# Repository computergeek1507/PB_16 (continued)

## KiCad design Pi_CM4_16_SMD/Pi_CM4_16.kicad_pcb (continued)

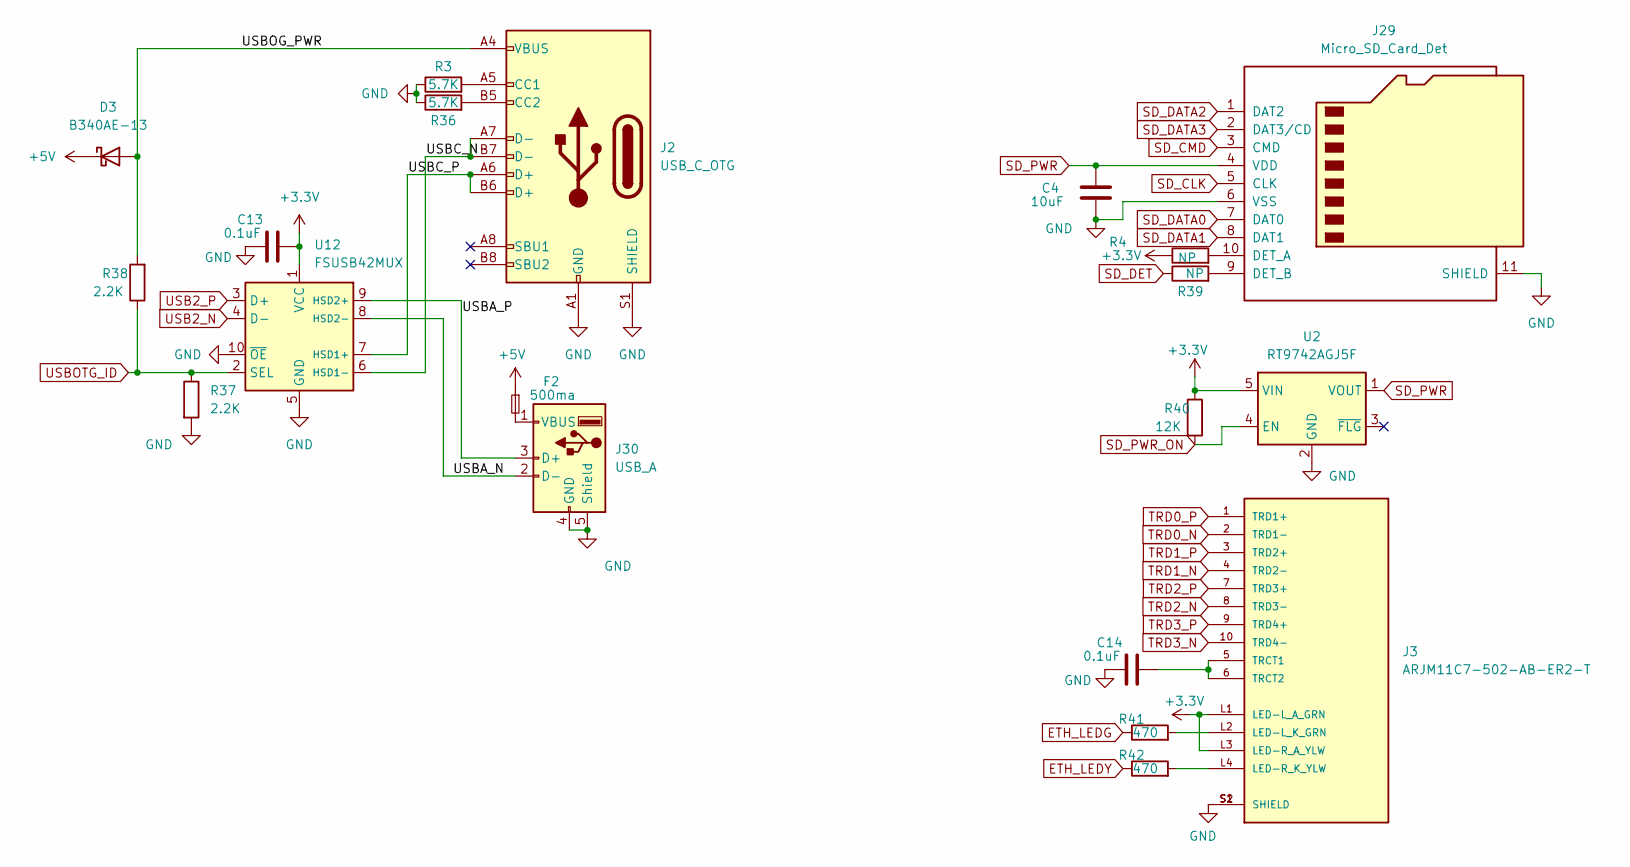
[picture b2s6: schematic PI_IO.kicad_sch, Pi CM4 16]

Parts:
C4: 10uF; C_0603_1608Metric_Pad1.08x0.95mm_HandSolder
C13, C14: 0.1uF; C_0603_1608Metric_Pad1.08x0.95mm_HandSolder; MPN CL10B104KB8NNWC; Digi-Key_PN 1276-1935-2-ND
D3: B340AE-13; D_SMA
F2: 500ma; Fuse_BelFuse_0ZRE0005FF_L8.3mm_W3.8mm
J2: USB_C_OTG; TYPE-C-31-M-12
J3: ARJM11C7-502-AB-ER2-T; ABRACON_ARJM11C7-502-AB-ER2-T; PARTREV 04.22.2019
J29: Micro_SD_Card_Det; microSD_HC_Molex_104031-0811
J30: USB_A; USB_A_Molex_105057_Vertical
R3, R36: 5.7K; R_0603_1608Metric_Pad0.98x0.95mm_HandSolder
R4, R39: NP; R_0603_1608Metric_Pad0.98x0.95mm_HandSolder
R37, R38: 2.2K; R_0603_1608Metric_Pad0.98x0.95mm_HandSolder
R40: 12K; R_0603_1608Metric_Pad0.98x0.95mm_HandSolder
R41, R42: 470; R_0603_1608Metric_Pad0.98x0.95mm_HandSolder
U2: RT9742AGJ5F; TSOT-23-5
U12: FSUSB42MUX; MSOP-10_3x3mm_P0.5mm

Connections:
+3.3V: C13.1, J3.L1 (LED-L_A_GRN), J3.L3 (LED-R_A_YLW), R4.1, R40.1, U2.5 (VIN), U12.1 (VCC); also elsewhere on the board
+5V: D3.1 (K), F2.1; also elsewhere on the board
/PI IO/USBA_N: J30.2 (D-), U12.8 (HSD2-)
/PI IO/USBA_P: J30.3 (D+), U12.9 (HSD2+)
/PI IO/USBC_N: J2.A7 (D-), J2.B7 (D-), U12.6 (HSD1-)
/PI IO/USBC_P: J2.A6 (D+), J2.B6 (D+), U12.7 (HSD1+)
/PI IO/USBOG_PWR: D3.2 (A), J2.A4 (VBUS), J2.A9 (VBUS), J2.B4 (VBUS), J2.B9 (VBUS), R38.2
ETH_LEDG: R41.1; also elsewhere on the board
ETH_LEDY: R42.1; also elsewhere on the board
GND: C4.1, C13.2, C14.2, J2.A1 (GND), J2.A12 (GND), J2.B1 (GND), J2.B12 (GND), J2.S1 (SHIELD), J3.S1 (SHIELD), J3.S2 (SHIELD), J29.6 (VSS), J29.11 (SHIELD), J30.4 (GND), J30.5 (Shield), R3.1, R36.1, R37.2, U2.2 (GND), U12.5 (GND), U12.10 (~OE); also elsewhere on the board
unnamed: C14.1, J3.5 (TRCT1), J3.6 (TRCT2)
unnamed: F2.2, J30.1 (VBUS)
unnamed: J2.A5 (CC1), R3.2
unnamed: J2.B5 (CC2), R36.2
unnamed: J3.L2 (LED-L_K_GRN), R41.2
unnamed: J3.L4 (LED-R_K_YLW), R42.2
unnamed: J29.9 (DET_B), R39.2
unnamed: J29.10 (DET_A), R4.2
SD_CLK: J29.5 (CLK); also elsewhere on the board
SD_CMD: J29.3 (CMD); also elsewhere on the board
SD_DATA0: J29.7 (DAT0); also elsewhere on the board
SD_DATA1: J29.8 (DAT1); also elsewhere on the board
SD_DATA2: J29.1 (DAT2); also elsewhere on the board
SD_DATA3: J29.2 (DAT3/CD); also elsewhere on the board
SD_DET: R39.1; also elsewhere on the board
SD_PWR: C4.2, J29.4 (VDD), U2.1 (VOUT)
SD_PWR_ON: R40.2, U2.4 (EN); also elsewhere on the board
TRD0_N: J3.2 (TRD1-); also elsewhere on the board
TRD0_P: J3.1 (TRD1+); also elsewhere on the board
TRD1_N: J3.4 (TRD2-); also elsewhere on the board
TRD1_P: J3.3 (TRD2+); also elsewhere on the board
TRD2_N: J3.8 (TRD3-); also elsewhere on the board
TRD2_P: J3.7 (TRD3+); also elsewhere on the board
TRD3_N: J3.10 (TRD4-); also elsewhere on the board
TRD3_P: J3.9 (TRD4+); also elsewhere on the board
USB2_N: U12.4 (D-); also elsewhere on the board
USB2_P: U12.3 (D+); also elsewhere on the board
USBOTG_ID: R37.1, R38.1, U12.2 (SEL); also elsewhere on the board

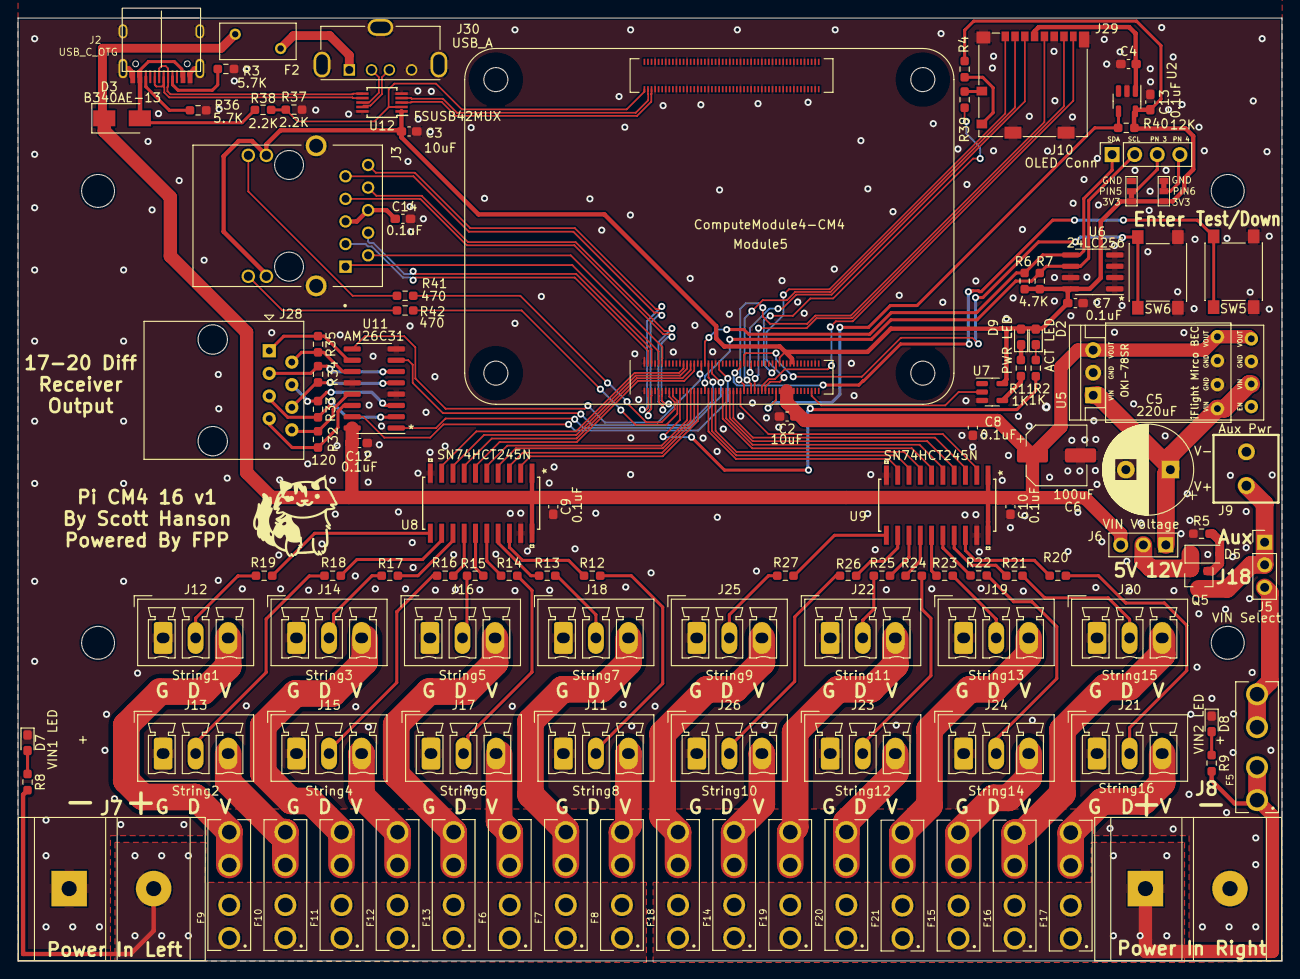
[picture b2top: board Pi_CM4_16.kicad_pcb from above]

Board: 2 copper layers, 142.1 x 106.0 mm, 117 parts (0 on the bottom side), 134 nets.

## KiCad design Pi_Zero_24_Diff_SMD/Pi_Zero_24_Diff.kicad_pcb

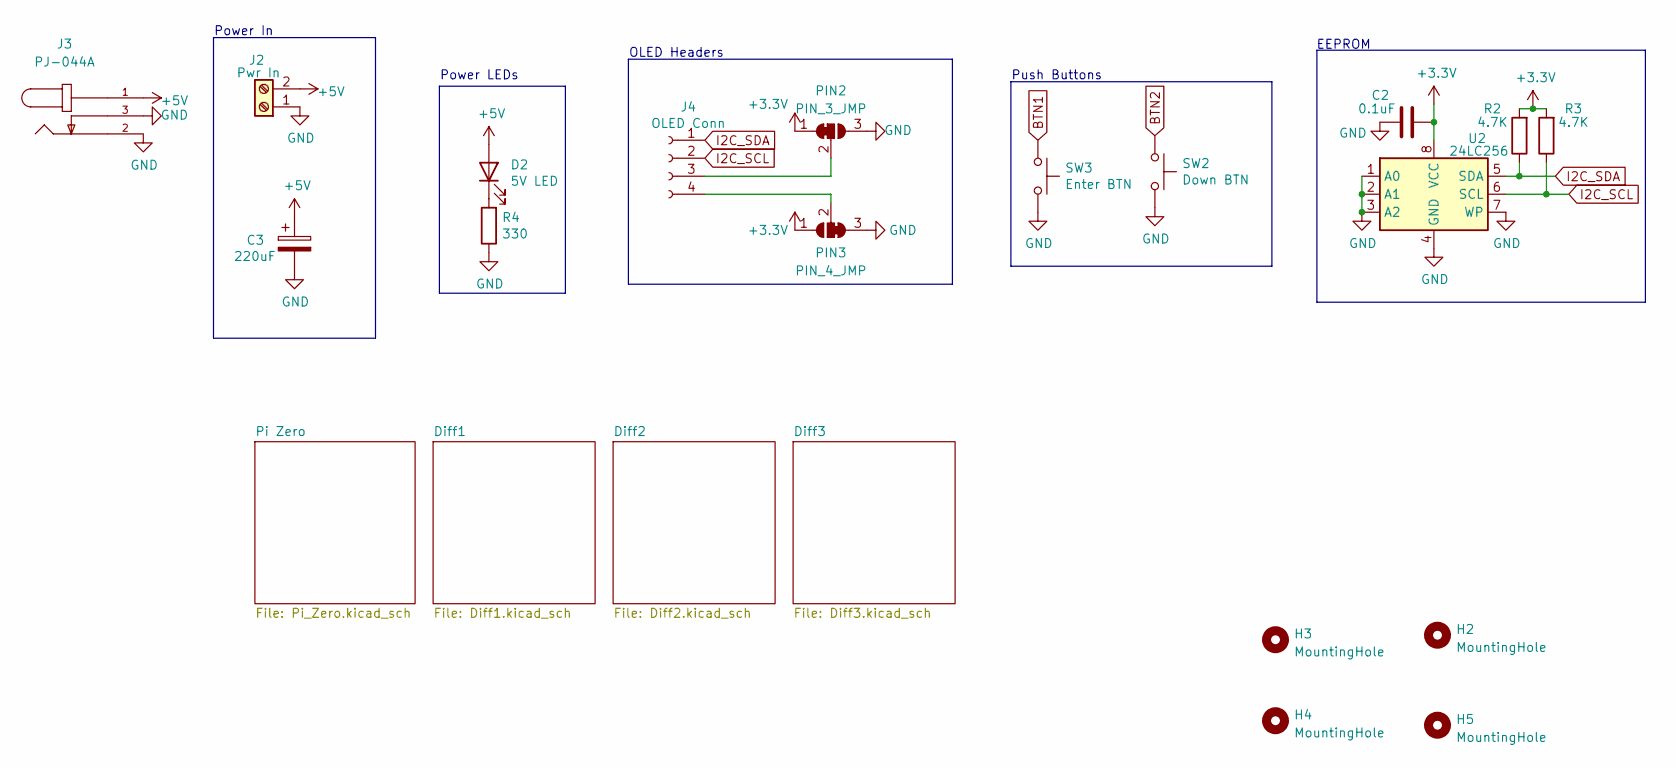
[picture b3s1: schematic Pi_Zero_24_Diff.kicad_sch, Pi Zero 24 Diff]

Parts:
C2: 0.1uF; C_0603_1608Metric_Pad1.08x0.95mm_HandSolder; MPN CL10B104KB8NNWC; Digi-Key_PN 1276-1935-2-ND
C3: 220uF; CP_Radial_D10.0mm_P5.00mm; MPN ECA-1HM221; Digi-Key_PN P5183-ND
D2: 5V LED; LED_0603_1608Metric_Pad1.05x0.95mm_HandSolder; MPN LTST-C190KRKT; Digi-Key_PN 160-1436-2-ND
H2, H3, H4, H5: MountingHole; MountingHole_3.7mm
J2: Pwr In; PHOENIX_MKDS1_2-3.81; MPN 1727010; Digi-Key_PN 277-1947-ND
J3: PJ-044A; CUI_PJ-044A; PARTREV 1.02; Digi-Key_PN CP-044A-ND
J4: OLED Conn; PinSocket_1x04_P2.54mm_Vertical; MPN PPTC041LFBN-RC; Digi-Key_PN S7002-ND
PIN2: PIN_3_JMP; SolderJumper-3_P1mm_Bridged12
PIN3: PIN_4_JMP; SolderJumper-3_P1mm_Bridged23
R2, R3: 4.7K; R_0603_1608Metric_Pad0.98x0.95mm_HandSolder; MPN RC0603JR-074K7L; Digi-Key_PN 311-4.7KGRCT-ND
R4: 330; R_0603_1608Metric_Pad0.98x0.95mm_HandSolder; LCSC C23138
SW2: Down BTN; SW_Push_1P1T_NO_6x6mm_H9.5mm; MPN PTS645SL50SMTR92 LFS; Digi-Key_PN CKN9088CT-ND
SW3: Enter BTN; SW_Push_1P1T_NO_6x6mm_H9.5mm; MPN PTS645SL50SMTR92 LFS; Digi-Key_PN CKN9088CT-ND
U2: 24LC256; SOIC-8_3.9x4.9mm_P1.27mm; MPN 24LC256T-I/SN; Digi-Key_PN 24LC256T-I/SNCT-ND

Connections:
+3V3: C2.1, PIN2.1 (A), PIN3.1 (A), R2.2, R3.2, U2.8 (VCC); also elsewhere on the board
+5V: C3.1, D2.2 (A), J2.2, J3.1; also elsewhere on the board
BTN1: SW3.1; also elsewhere on the board
BTN2: SW2.1; also elsewhere on the board
GND: C2.2, C3.2, J2.1, J3.2, J3.3, PIN2.3 (B), PIN3.3 (B), R4.1, SW2.2, SW3.2, U2.1 (A0), U2.2 (A1), U2.3 (A2), U2.4 (GND), U2.7 (WP); also elsewhere on the board
I2C_SCL: J4.2, R3.1, U2.6 (SCL); also elsewhere on the board
I2C_SDA: J4.1, R2.1, U2.5 (SDA); also elsewhere on the board
unnamed: D2.1 (K), R4.2
unnamed: J4.3, PIN2.2 (C)
unnamed: J4.4, PIN3.2 (C)

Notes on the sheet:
Power LEDs
Power In
OLED Headers
Push Buttons
EEPROM

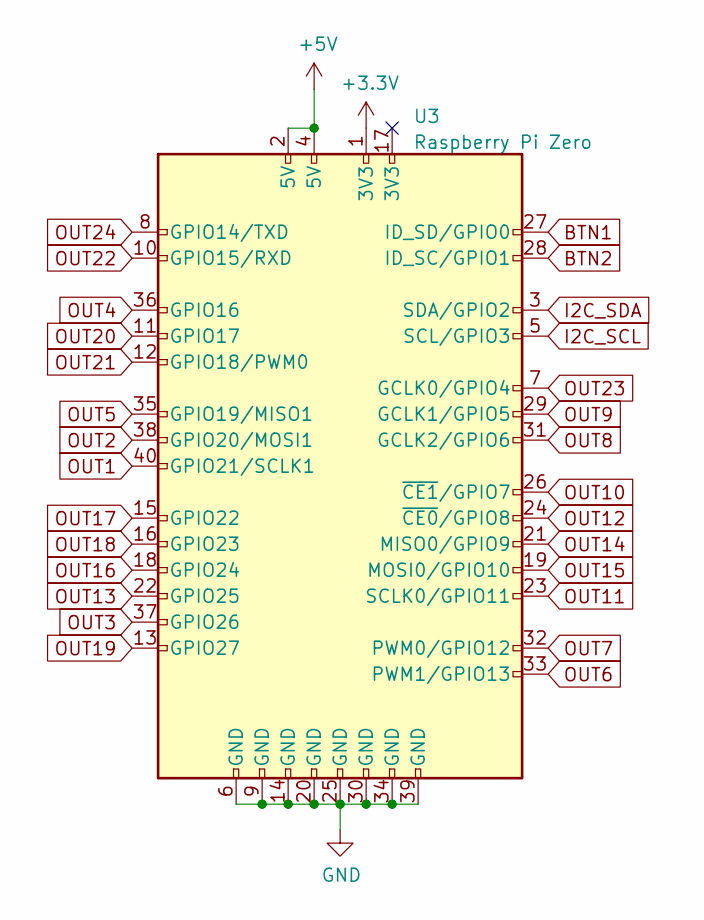
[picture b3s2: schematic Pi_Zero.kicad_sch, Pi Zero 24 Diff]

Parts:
U3: Raspberry Pi Zero; Raspberry_Pi_Zero_Socketed_THT_FaceDown_MountingHoles

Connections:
+3V3: U3.1 (3V3); also elsewhere on the board
+5V: U3.2 (5V), U3.4 (5V); also elsewhere on the board
BTN1: U3.27 (ID_SD/GPIO0); also elsewhere on the board
BTN2: U3.28 (ID_SC/GPIO1); also elsewhere on the board
GND: U3.6 (GND), U3.9 (GND), U3.14 (GND), U3.20 (GND), U3.25 (GND), U3.30 (GND), U3.34 (GND), U3.39 (GND); also elsewhere on the board
I2C_SCL: U3.5 (SCL/GPIO3); also elsewhere on the board
I2C_SDA: U3.3 (SDA/GPIO2); also elsewhere on the board
OUT1: U3.40 (GPIO21/SCLK1); also elsewhere on the board
OUT2: U3.38 (GPIO20/MOSI1); also elsewhere on the board
OUT3: U3.37 (GPIO26); also elsewhere on the board
OUT4: U3.36 (GPIO16); also elsewhere on the board
OUT5: U3.35 (GPIO19/MISO1); also elsewhere on the board
OUT6: U3.33 (PWM1/GPIO13); also elsewhere on the board
OUT7: U3.32 (PWM0/GPIO12); also elsewhere on the board
OUT8: U3.31 (GCLK2/GPIO6); also elsewhere on the board
OUT9: U3.29 (GCLK1/GPIO5); also elsewhere on the board
OUT10: U3.26 (~CE1/GPIO7); also elsewhere on the board
OUT11: U3.23 (SCLK0/GPIO11); also elsewhere on the board
OUT12: U3.24 (~CE0/GPIO8); also elsewhere on the board
OUT13: U3.22 (GPIO25); also elsewhere on the board
OUT14: U3.21 (MISO0/GPIO9); also elsewhere on the board
OUT15: U3.19 (MOSI0/GPIO10); also elsewhere on the board
OUT16: U3.18 (GPIO24); also elsewhere on the board
OUT17: U3.15 (GPIO22); also elsewhere on the board
OUT18: U3.16 (GPIO23); also elsewhere on the board
OUT19: U3.13 (GPIO27); also elsewhere on the board
OUT20: U3.11 (GPIO17); also elsewhere on the board
OUT21: U3.12 (GPIO18/PWM0); also elsewhere on the board
OUT22: U3.10 (GPIO15/RXD); also elsewhere on the board
OUT23: U3.7 (GCLK0/GPIO4); also elsewhere on the board
OUT24: U3.8 (GPIO14/TXD); also elsewhere on the board

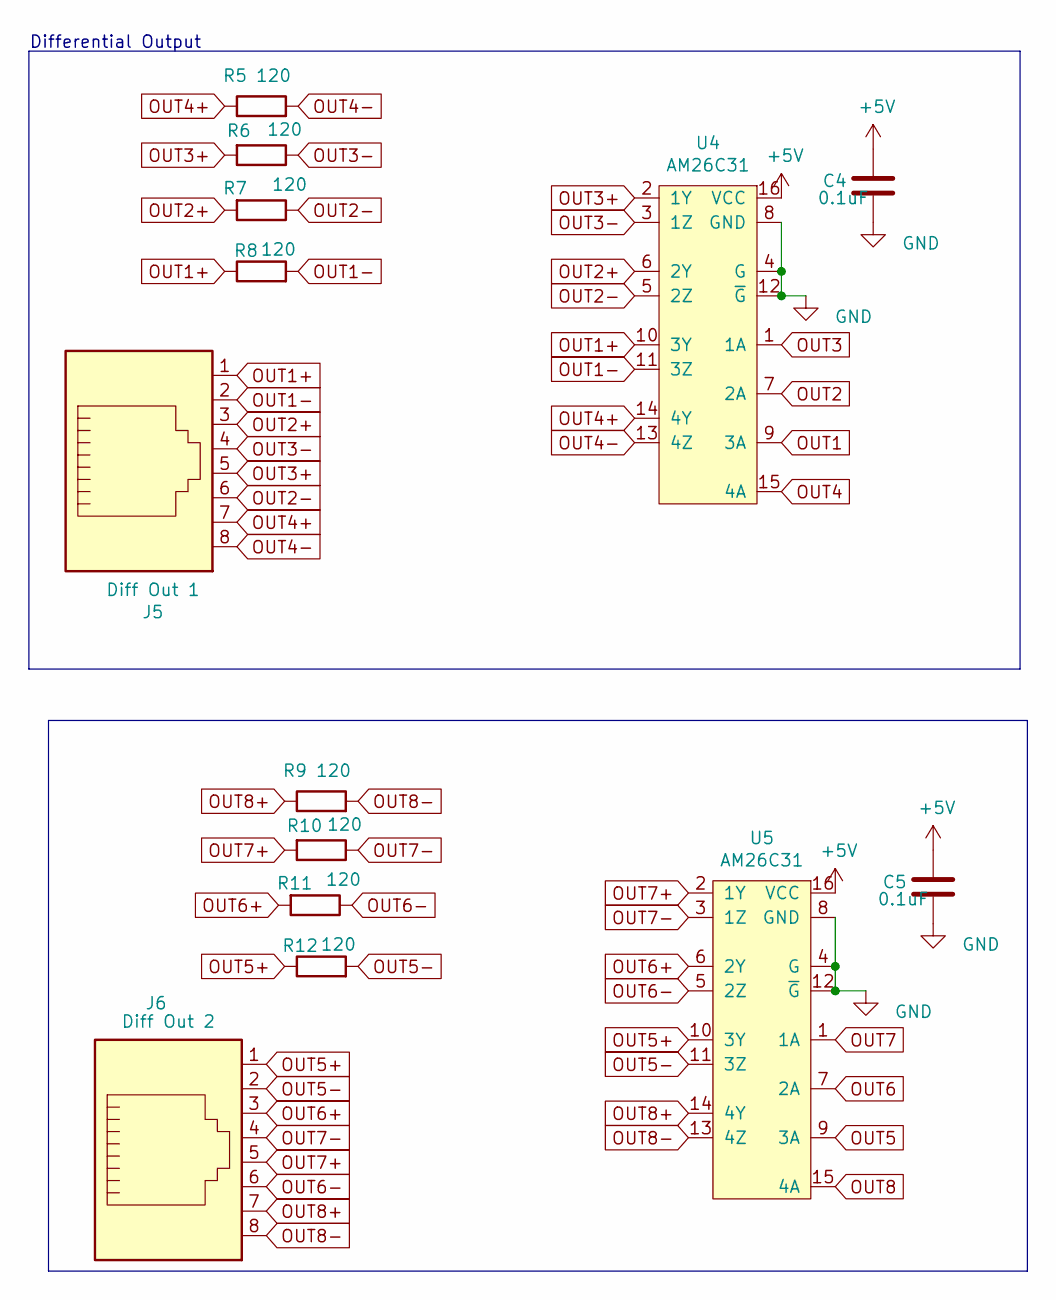
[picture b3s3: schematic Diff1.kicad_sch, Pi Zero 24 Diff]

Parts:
C4, C5: 0.1uF; C_0603_1608Metric_Pad1.08x0.95mm_HandSolder; MPN CL10B104KB8NNWC; Digi-Key_PN 1276-1935-2-ND
J5: Diff Out 1; RJ45_Amphenol_54602-x08_Horizontal; MPN X05ADIWA1DY1022; Digi-Key_PN AE10392-ND
J6: Diff Out 2; RJ45_Amphenol_54602-x08_Horizontal; MPN X05ADIWA1DY1022; Digi-Key_PN AE10392-ND
R5, R6, R7, R8, R9, R10, R11, R12: 120; R_0603_1608Metric_Pad0.98x0.95mm_HandSolder; MPN CRGCQ0603F120R; Digi-Key_PN A129677CT-ND
U4, U5: AM26C31; SOIC-16_3.9x9.9mm_P1.27mm; MPN AM26C31IDR; Farnell 4975637

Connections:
+5V: C4.1, C5.1, U4.16 (VCC), U5.16 (VCC); also elsewhere on the board
GND: C4.2, C5.2, U4.4 (G), U4.8 (GND), U4.12 (~G), U5.4 (G), U5.8 (GND), U5.12 (~G); also elsewhere on the board
OUT1: U4.9 (3A); also elsewhere on the board
OUT1+: J5.1, R8.1, U4.10 (3Y)
OUT1-: J5.2, R8.2, U4.11 (3Z)
OUT2: U4.7 (2A); also elsewhere on the board
OUT2+: J5.3, R7.2, U4.6 (2Y)
OUT2-: J5.6, R7.1, U4.5 (2Z)
OUT3: U4.1 (1A); also elsewhere on the board
OUT3+: J5.5, R6.2, U4.2 (1Y)
OUT3-: J5.4, R6.1, U4.3 (1Z)
OUT4: U4.15 (4A); also elsewhere on the board
OUT4+: J5.7, R5.1, U4.14 (4Y)
OUT4-: J5.8, R5.2, U4.13 (4Z)
OUT5: U5.9 (3A); also elsewhere on the board
OUT5+: J6.1, R12.1, U5.10 (3Y)
OUT5-: J6.2, R12.2, U5.11 (3Z)
OUT6: U5.7 (2A); also elsewhere on the board
OUT6+: J6.3, R11.2, U5.6 (2Y)
OUT6-: J6.6, R11.1, U5.5 (2Z)
OUT7: U5.1 (1A); also elsewhere on the board
OUT7+: J6.5, R10.2, U5.2 (1Y)
OUT7-: J6.4, R10.1, U5.3 (1Z)
OUT8: U5.15 (4A); also elsewhere on the board
OUT8+: J6.7, R9.1, U5.14 (4Y)
OUT8-: J6.8, R9.2, U5.13 (4Z)

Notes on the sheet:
Differential Output

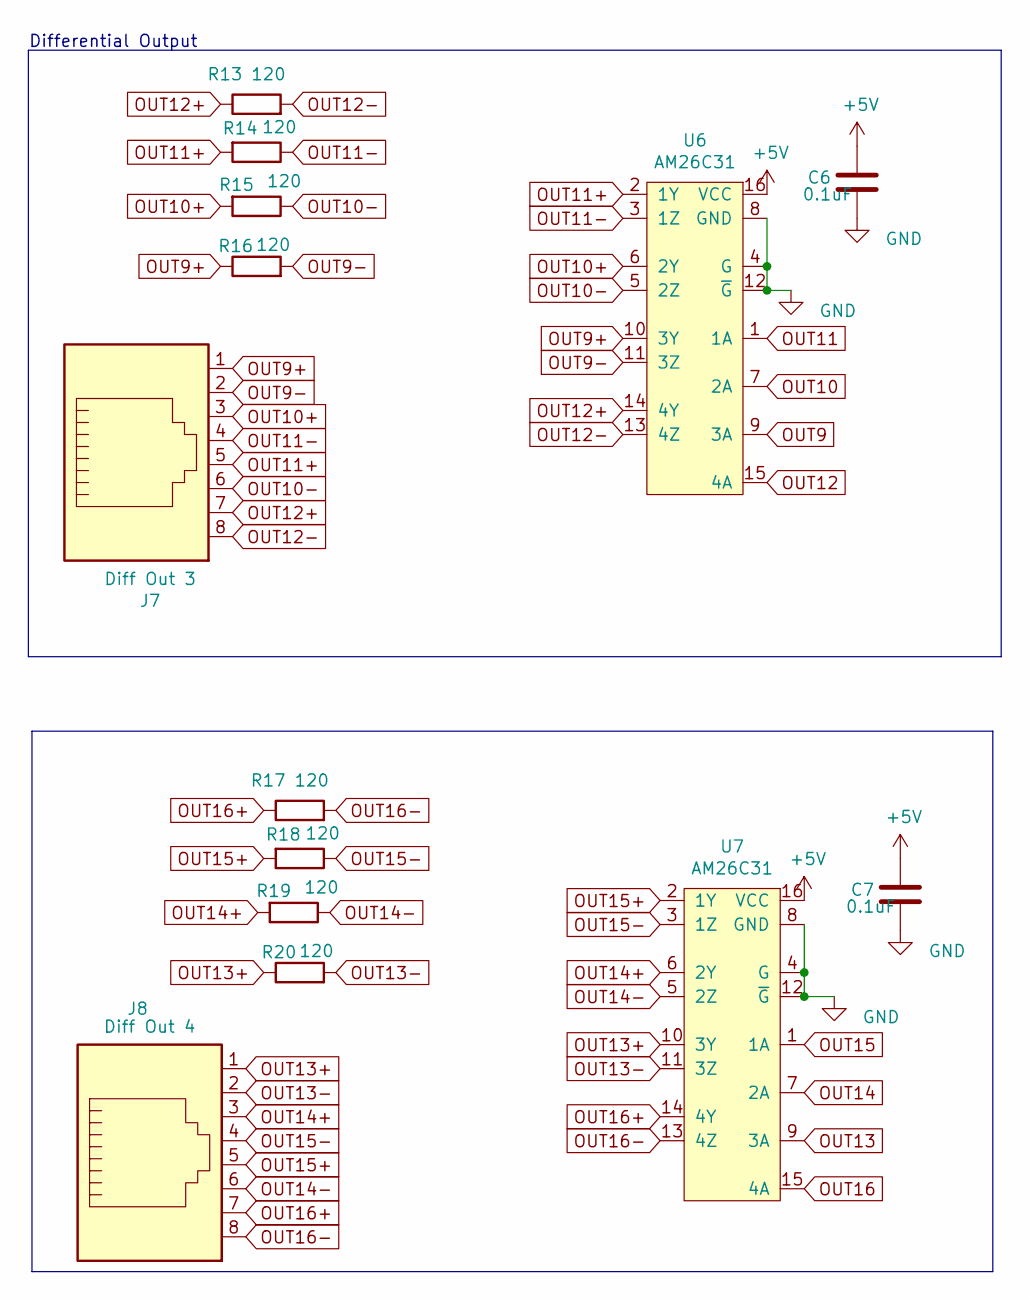
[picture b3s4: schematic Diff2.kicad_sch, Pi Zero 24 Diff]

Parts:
C6, C7: 0.1uF; C_0603_1608Metric_Pad1.08x0.95mm_HandSolder; MPN CL10B104KB8NNWC; Digi-Key_PN 1276-1935-2-ND
J7: Diff Out 3; RJ45_Amphenol_54602-x08_Horizontal; MPN X05ADIWA1DY1022; Digi-Key_PN AE10392-ND
J8: Diff Out 4; RJ45_Amphenol_54602-x08_Horizontal; MPN X05ADIWA1DY1022; Digi-Key_PN AE10392-ND
R13, R14, R15, R16, R17, R18, R19, R20: 120; R_0603_1608Metric_Pad0.98x0.95mm_HandSolder; MPN CRGCQ0603F120R; Digi-Key_PN A129677CT-ND
U6, U7: AM26C31; SOIC-16_3.9x9.9mm_P1.27mm; MPN AM26C31IDR; Farnell 4975637

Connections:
+5V: C6.1, C7.1, U6.16 (VCC), U7.16 (VCC); also elsewhere on the board
GND: C6.2, C7.2, U6.4 (G), U6.8 (GND), U6.12 (~G), U7.4 (G), U7.8 (GND), U7.12 (~G); also elsewhere on the board
OUT9: U6.9 (3A); also elsewhere on the board
OUT9+: J7.1, R16.1, U6.10 (3Y)
OUT9-: J7.2, R16.2, U6.11 (3Z)
OUT10: U6.7 (2A); also elsewhere on the board
OUT10+: J7.3, R15.2, U6.6 (2Y)
OUT10-: J7.6, R15.1, U6.5 (2Z)
OUT11: U6.1 (1A); also elsewhere on the board
OUT11+: J7.5, R14.2, U6.2 (1Y)
OUT11-: J7.4, R14.1, U6.3 (1Z)
OUT12: U6.15 (4A); also elsewhere on the board
OUT12+: J7.7, R13.1, U6.14 (4Y)
OUT12-: J7.8, R13.2, U6.13 (4Z)
OUT13: U7.9 (3A); also elsewhere on the board
OUT13+: J8.1, R20.1, U7.10 (3Y)
OUT13-: J8.2, R20.2, U7.11 (3Z)
OUT14: U7.7 (2A); also elsewhere on the board
OUT14+: J8.3, R19.2, U7.6 (2Y)
OUT14-: J8.6, R19.1, U7.5 (2Z)
OUT15: U7.1 (1A); also elsewhere on the board
OUT15+: J8.5, R18.2, U7.2 (1Y)
OUT15-: J8.4, R18.1, U7.3 (1Z)
OUT16: U7.15 (4A); also elsewhere on the board
OUT16+: J8.7, R17.1, U7.14 (4Y)
OUT16-: J8.8, R17.2, U7.13 (4Z)

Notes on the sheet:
Differential Output

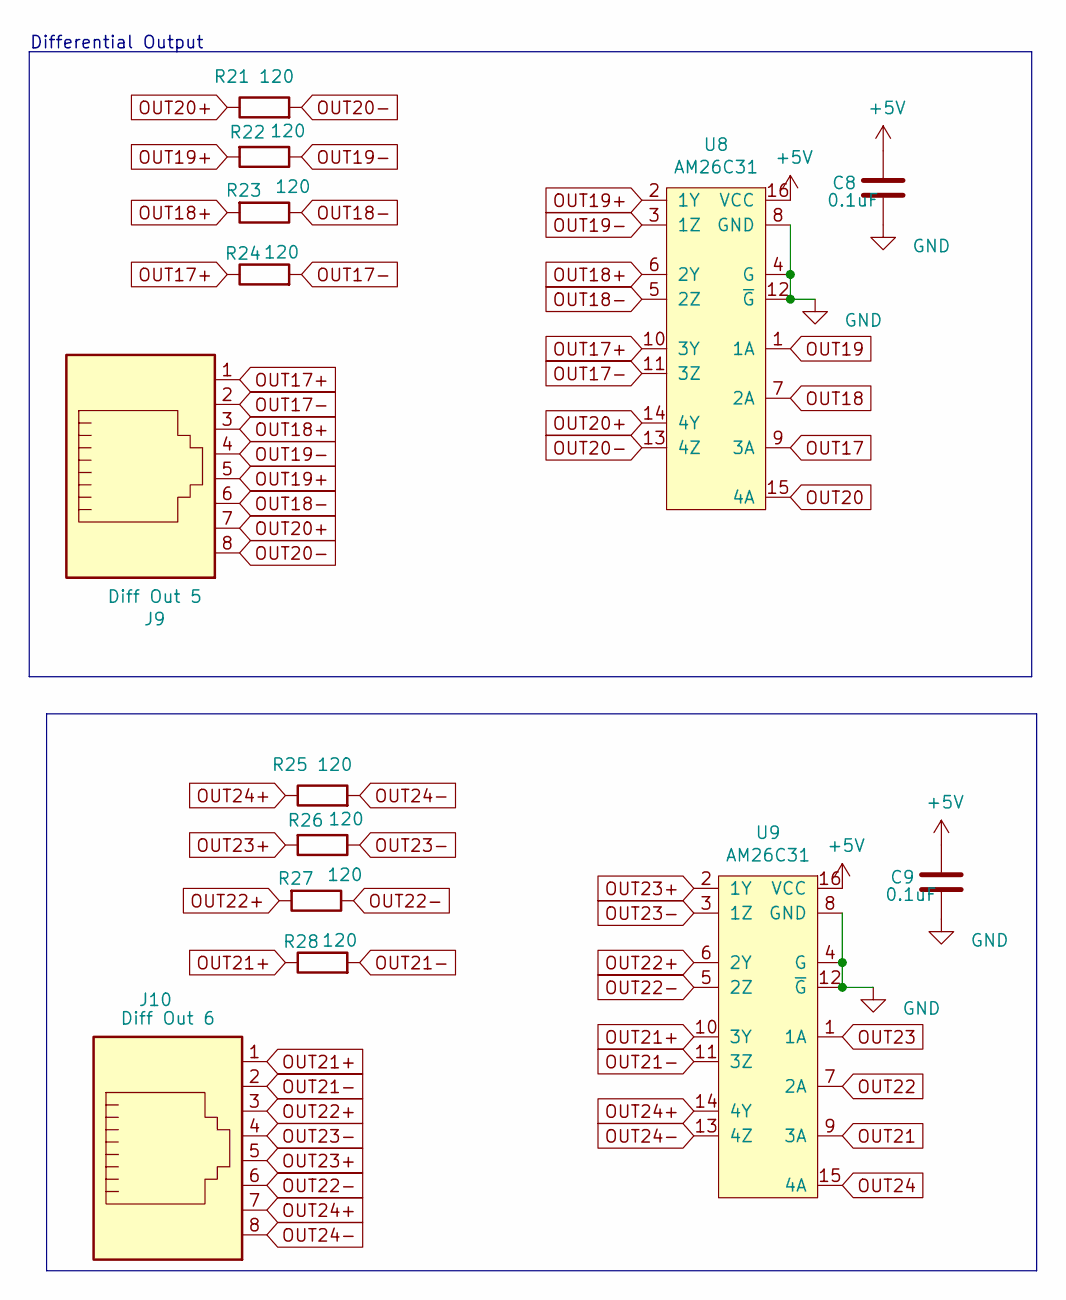
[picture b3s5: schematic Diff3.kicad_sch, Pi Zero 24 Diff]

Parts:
C8, C9: 0.1uF; C_0603_1608Metric_Pad1.08x0.95mm_HandSolder; MPN CL10B104KB8NNWC; Digi-Key_PN 1276-1935-2-ND
J9: Diff Out 5; RJ45_Amphenol_54602-x08_Horizontal; MPN X05ADIWA1DY1022; Digi-Key_PN AE10392-ND
J10: Diff Out 6; RJ45_Amphenol_54602-x08_Horizontal; MPN X05ADIWA1DY1022; Digi-Key_PN AE10392-ND
R21, R22, R23, R24, R25, R26, R27, R28: 120; R_0603_1608Metric_Pad0.98x0.95mm_HandSolder; MPN CRGCQ0603F120R; Digi-Key_PN A129677CT-ND
U8, U9: AM26C31; SOIC-16_3.9x9.9mm_P1.27mm; MPN AM26C31IDR; Farnell 4975637

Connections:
+5V: C8.1, C9.1, U8.16 (VCC), U9.16 (VCC); also elsewhere on the board
GND: C8.2, C9.2, U8.4 (G), U8.8 (GND), U8.12 (~G), U9.4 (G), U9.8 (GND), U9.12 (~G); also elsewhere on the board
OUT17: U8.9 (3A); also elsewhere on the board
OUT17+: J9.1, R24.1, U8.10 (3Y)
OUT17-: J9.2, R24.2, U8.11 (3Z)
OUT18: U8.7 (2A); also elsewhere on the board
OUT18+: J9.3, R23.2, U8.6 (2Y)
OUT18-: J9.6, R23.1, U8.5 (2Z)
OUT19: U8.1 (1A); also elsewhere on the board
OUT19+: J9.5, R22.2, U8.2 (1Y)
OUT19-: J9.4, R22.1, U8.3 (1Z)
OUT20: U8.15 (4A); also elsewhere on the board
OUT20+: J9.7, R21.1, U8.14 (4Y)
OUT20-: J9.8, R21.2, U8.13 (4Z)
OUT21: U9.9 (3A); also elsewhere on the board
OUT21+: J10.1, R28.1, U9.10 (3Y)
OUT21-: J10.2, R28.2, U9.11 (3Z)
OUT22: U9.7 (2A); also elsewhere on the board
OUT22+: J10.3, R27.2, U9.6 (2Y)
OUT22-: J10.6, R27.1, U9.5 (2Z)
OUT23: U9.1 (1A); also elsewhere on the board
OUT23+: J10.5, R26.2, U9.2 (1Y)
OUT23-: J10.4, R26.1, U9.3 (1Z)
OUT24: U9.15 (4A); also elsewhere on the board
OUT24+: J10.7, R25.1, U9.14 (4Y)
OUT24-: J10.8, R25.2, U9.13 (4Z)

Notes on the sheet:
Differential Output

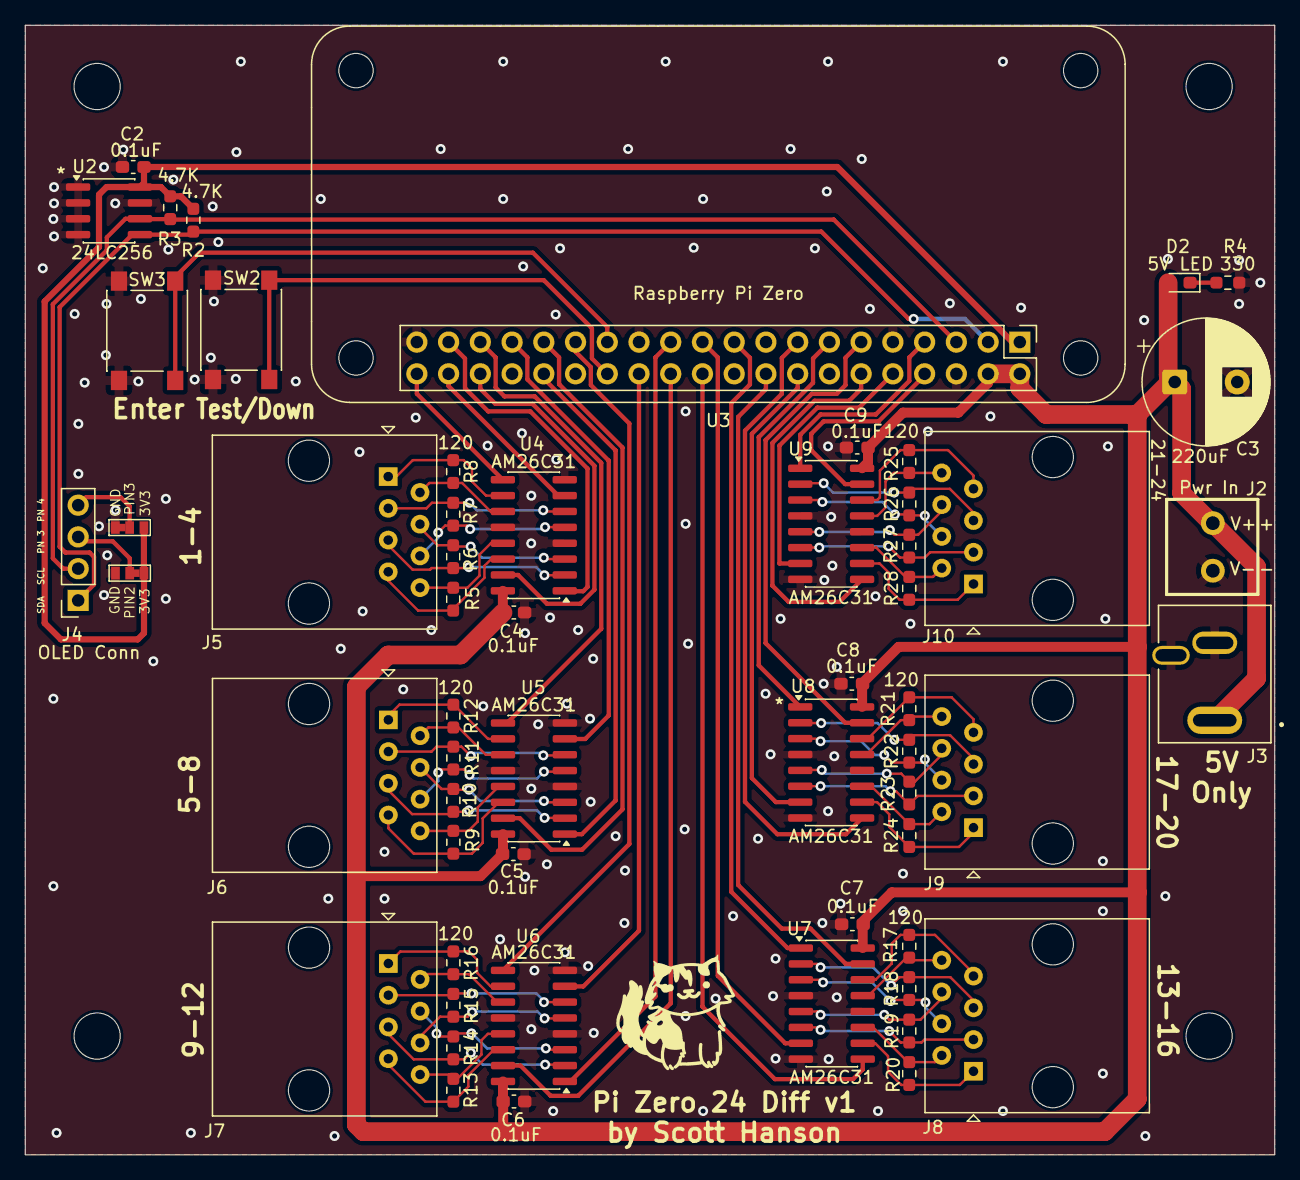
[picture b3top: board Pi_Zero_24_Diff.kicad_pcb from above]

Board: 2 copper layers, 100.0 x 90.4 mm, 61 parts (1 on the bottom side), 82 nets.

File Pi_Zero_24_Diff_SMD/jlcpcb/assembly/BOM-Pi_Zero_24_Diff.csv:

Comment,Designator,Footprint,LCSC
Down BTN,"SW2,SW3",SW_Push_1P1T_NO_6x6mm_H9.5mm,C127509
0.1uF,"C2,C4,C5,C6,C7,C8,C9",C_0603_1608Metric_Pad1.08x0.95mm_HandSolder,C14663
AM26C31,"U4,U5,U6,U7,U8,U9",SOIC-16_3.9x9.9mm_P1.27mm,C157476
OLED Conn,J4,PinSocket_1x04_P2.54mm_Vertical,C225501
120,"R10,R11,R12,R13,R14,R15,R16,R17,R18,R19,R20,R21,R22,R23,R24,R25,R26,R27,R28,R5,R6,R7,R8,R9",R_0603_1608Metric_Pad0.98x0.95mm_HandSolder,C22787
5V LED,D2,LED_0603_1608Metric_Pad1.05x0.95mm_HandSolder,C2286
330,R4,R_0603_1608Metric_Pad0.98x0.95mm_HandSolder,C23138
4.7K,"R2,R3",R_0603_1608Metric_Pad0.98x0.95mm_HandSolder,C23162
220uF,C3,CP_Radial_D10.0mm_P5.00mm,C338228
24LC256,U2,SOIC-8_3.9x4.9mm_P1.27mm,C6482
Pwr In,J2,PHOENIX_MKDS1_2-3.81,C69811
Diff Out 6,"J10,J5,J6,J7,J8,J9",RJ45_Amphenol_54602-x08_Horizontal,C86492
Raspberry Pi Zero,U3,Raspberry_Pi_Zero_Socketed_THT_FaceDown_MountingHoles,

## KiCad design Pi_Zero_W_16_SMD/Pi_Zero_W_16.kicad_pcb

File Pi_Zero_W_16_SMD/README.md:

# Copyright and Disclaimer
Copyright: Scott Hanson

This documentation describes Open Hardware and is licensed under the CERN Open Hardware Licence Version 2 - Strongly Reciprocal. (CERN-OHL-S)

You may redistribute and modify this documentation under the terms of the CERN OHL-S-v2 (https://ohwr.org/cern_ohl_s_v2.txt). This documentation is distributed WITHOUT ANY EXPRESS OR IMPLIED WARRANTY, INCLUDING OF MERCHANTABILITY, SATISFACTORY QUALITY AND FITNESS FOR A PARTICULAR PURPOSE. Please see the CERN OHL v2-S for applicable conditions

**Under CERN OHL-S-v2, derivative work must be publicy released as defined in subsection 3.3**

# Pi Zero W 16

**Never Built or tested**

The Pi Zero W 16 is a surface mount(SMD) controller with 16 local pixel ports and two remote receiver port(8 remote ports). A total of 24 pixel outputs. All the design files are open source and available on github.

## [Interactive BOM](https://computergeek1507.github.io/PB_16/Pi_Zero_W_16_SMD/bom/ibom)

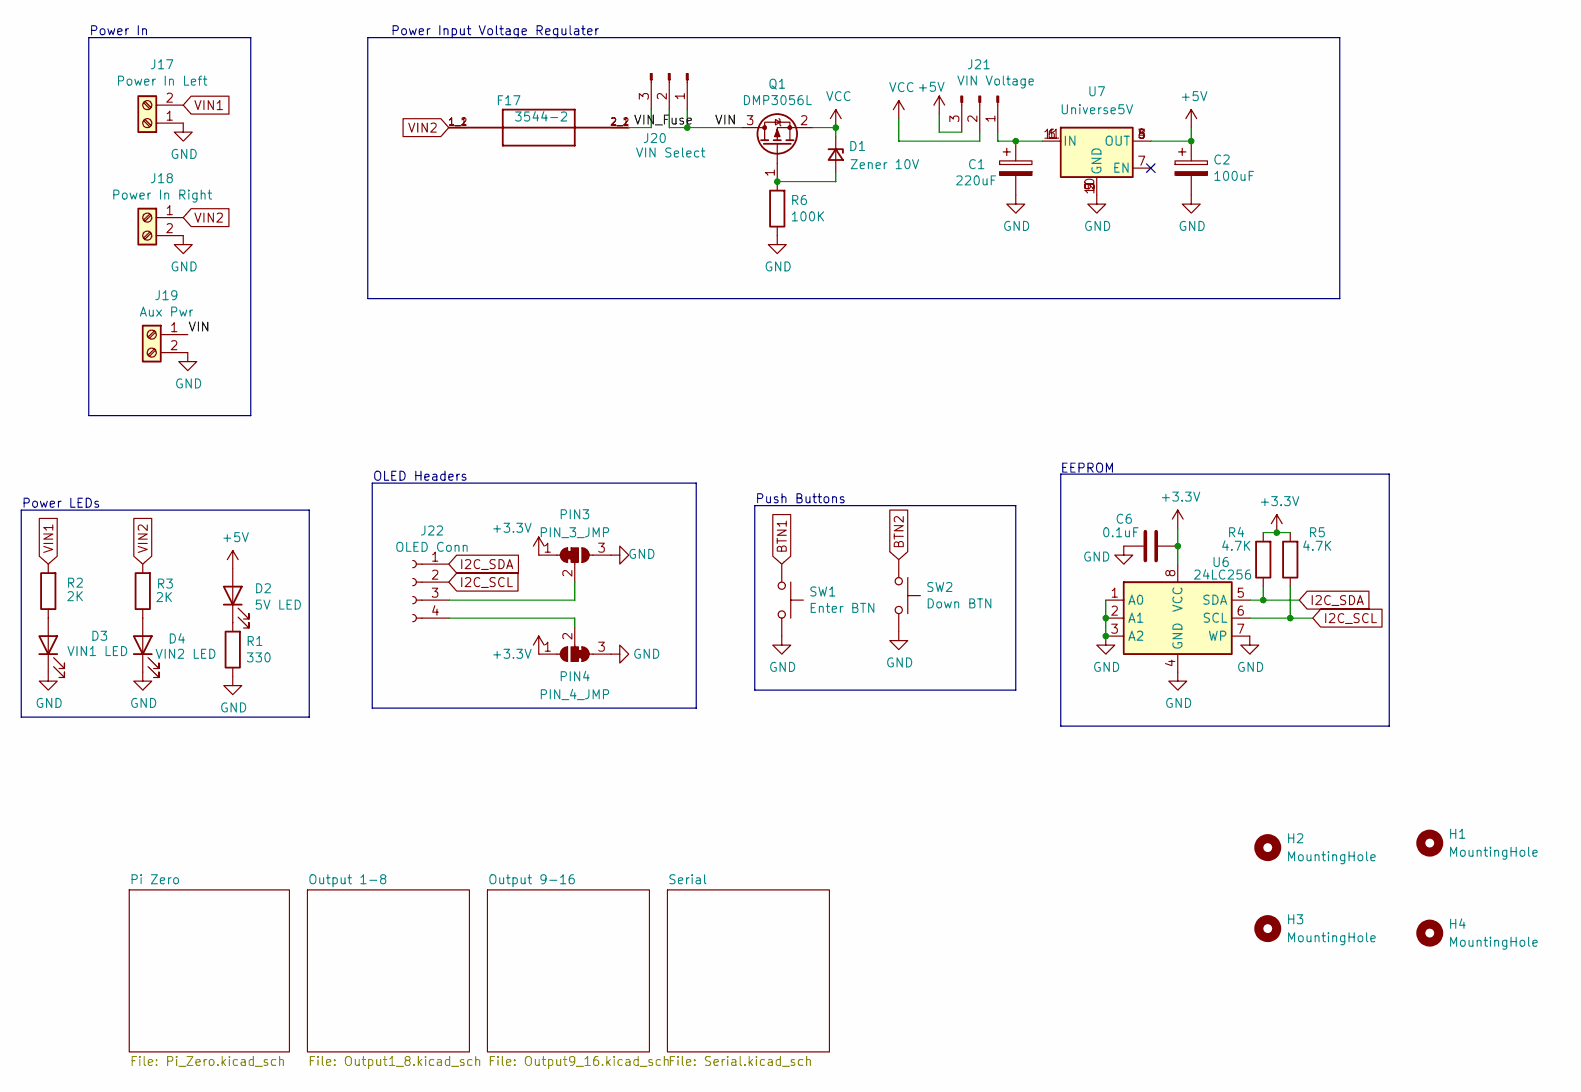
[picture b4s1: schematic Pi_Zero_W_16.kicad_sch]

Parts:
C1: 220uF; CP_Radial_D10.0mm_P5.00mm; MPN ECA-1HM221; Digi-Key_PN P5183-ND
C2: 100uF; CP_Elec_6.3x5.4_Nichicon; MPN UWX1C101MCL1GB; Digi-Key_PN 493-2105-1-ND
C6: 0.1uF; C_0603_1608Metric_Pad1.08x0.95mm_HandSolder; MPN CL10B104KB8NNWC; Digi-Key_PN 1276-1935-2-ND
D1: Zener 10V; D_SOD-123; MPN MMSZ5240B-7-F; Digi-Key_PN MMSZ5240B-FDICT-ND
D2: 5V LED; LED_0603_1608Metric_Pad1.05x0.95mm_HandSolder; MPN LTST-C190KRKT; Digi-Key_PN 160-1436-2-ND
D3: VIN1 LED; LED_0603_1608Metric_Pad1.05x0.95mm_HandSolder; MPN LTST-C190KRKT; Digi-Key_PN 160-1436-2-ND
D4: VIN2 LED; LED_0603_1608Metric_Pad1.05x0.95mm_HandSolder; MPN LTST-C190KRKT; Digi-Key_PN 160-1436-2-ND
F17: 3544-2; FUSE_3544-2; MPN 3544-2; Digi-Key_PN 36-3544-2-ND
H1, H2, H3, H4: MountingHole; MountingHole_3.7mm
J17: Power In Left; BARRIER_BLOCK_1ROW_2POS_P9.5MM; MPN OSTYK51102030; Digi-Key_PN ED2953-ND
J18: Power In Right; BARRIER_BLOCK_1ROW_2POS_P9.5MM; MPN OSTYK51102030; Digi-Key_PN ED2953-ND
J19: Aux Pwr; PHOENIX_MKDS1_2-3.81; MPN 1727010; Digi-Key_PN 277-1947-ND
J20: VIN Select; PinHeader_1x03_P2.54mm_Vertical; MPN 61300311121; Digi-Key_PN 732-5316-ND
J21: VIN Voltage; PinHeader_1x03_P2.54mm_Vertical; MPN 61300311121; Digi-Key_PN 732-5316-ND
J22: OLED Conn; PinSocket_1x04_P2.54mm_Vertical; MPN PPTC041LFBN-RC; Digi-Key_PN S7002-ND
PIN3: PIN_3_JMP; SolderJumper-3_P1mm_Bridged12
PIN4: PIN_4_JMP; SolderJumper-3_P1mm_Bridged23
Q1: DMP3056L; SOT-23; MPN DMP3056L-7; Digi-Key_PN DMP3056L-7DICT-ND
R1: 330; R_0603_1608Metric_Pad0.98x0.95mm_HandSolder; LCSC C23138
R2, R3: 2K; R_0603_1608Metric_Pad0.98x0.95mm_HandSolder; LCSC C4190
R4, R5: 4.7K; R_0603_1608Metric_Pad0.98x0.95mm_HandSolder; MPN RC0603JR-074K7L; Digi-Key_PN 311-4.7KGRCT-ND
R6: 100K; R_0603_1608Metric_Pad0.98x0.95mm_HandSolder; MPN RT0603BRD07100KL; Digi-Key_PN YAG1235CT-ND
SW1: Enter BTN; SW_Push_1P1T_NO_6x6mm_H9.5mm; MPN PTS645SL50SMTR92 LFS; Digi-Key_PN CKN9088CT-ND
SW2: Down BTN; SW_Push_1P1T_NO_6x6mm_H9.5mm; MPN PTS645SL50SMTR92 LFS; Digi-Key_PN CKN9088CT-ND
U6: 24LC256; SOIC-8_3.9x4.9mm_P1.27mm; MPN 24LC256T-I/SN; Digi-Key_PN 24LC256T-I/SNCT-ND
U7: Universe5V; Universal_5V_Horizontal

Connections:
+3V3: C6.1, PIN3.1 (A), PIN4.1 (A), R4.2, R5.2, U6.8 (VCC); also elsewhere on the board
+5V: C2.1, D2.2 (A), J21.3, U7.3 (OUT), U7.4 (OUT), U7.8 (OUT); also elsewhere on the board
/VIN: J19.1, J20.1, J20.2, Q1.3 (D)
/VIN_Fuse: F17.2_1 (2), F17.2_2 (2), J20.3
BTN1: SW1.1; also elsewhere on the board
BTN2: SW2.1; also elsewhere on the board
GND: C1.2, C2.2, C6.2, D3.1 (K), D4.1 (K), J17.1, J18.2, J19.2, PIN3.3 (B), PIN4.3 (B), R1.1, R6.1, SW1.2, SW2.2, U6.1 (A0), U6.2 (A1), U6.3 (A2), U6.4 (GND), U6.7 (WP), U7.2 (GND), U7.5 (GND), U7.9 (GND), U7.10 (GND); also elsewhere on the board
I2C_SCL: J22.2, R5.1, U6.6 (SCL); also elsewhere on the board
I2C_SDA: J22.1, R4.1, U6.5 (SDA); also elsewhere on the board
unnamed: C1.1, J21.1, U7.1 (IN), U7.6 (IN), U7.11 (IN)
unnamed: D1.2 (A), Q1.1 (G), R6.2
unnamed: D2.1 (K), R1.2
unnamed: D3.2 (A), R2.1
unnamed: D4.2 (A), R3.1
unnamed: J22.3, PIN3.2 (C)
unnamed: J22.4, PIN4.2 (C)
VCC: D1.1 (K), J21.2, Q1.2 (S)
VIN1: J17.2, R2.2; also elsewhere on the board
VIN2: F17.1_1 (1), F17.1_2 (1), J18.1, R3.2; also elsewhere on the board

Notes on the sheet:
Power LEDs
Power In
OLED Headers
Push Buttons
Power Input Voltage Regulater
EEPROM
